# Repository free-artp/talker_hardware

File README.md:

Eagle project about ATMEGA168 for wood's sort device (p-dok.ru)

Print out:
	Bottom
	Pad
	Via
	Dimension
	Holes

Mirror + Pos.coord

Offcet:
X = 2.2 inch
Y = 7 inch

Hot iron - 40 sec, full power, by my hand not a body
11:38

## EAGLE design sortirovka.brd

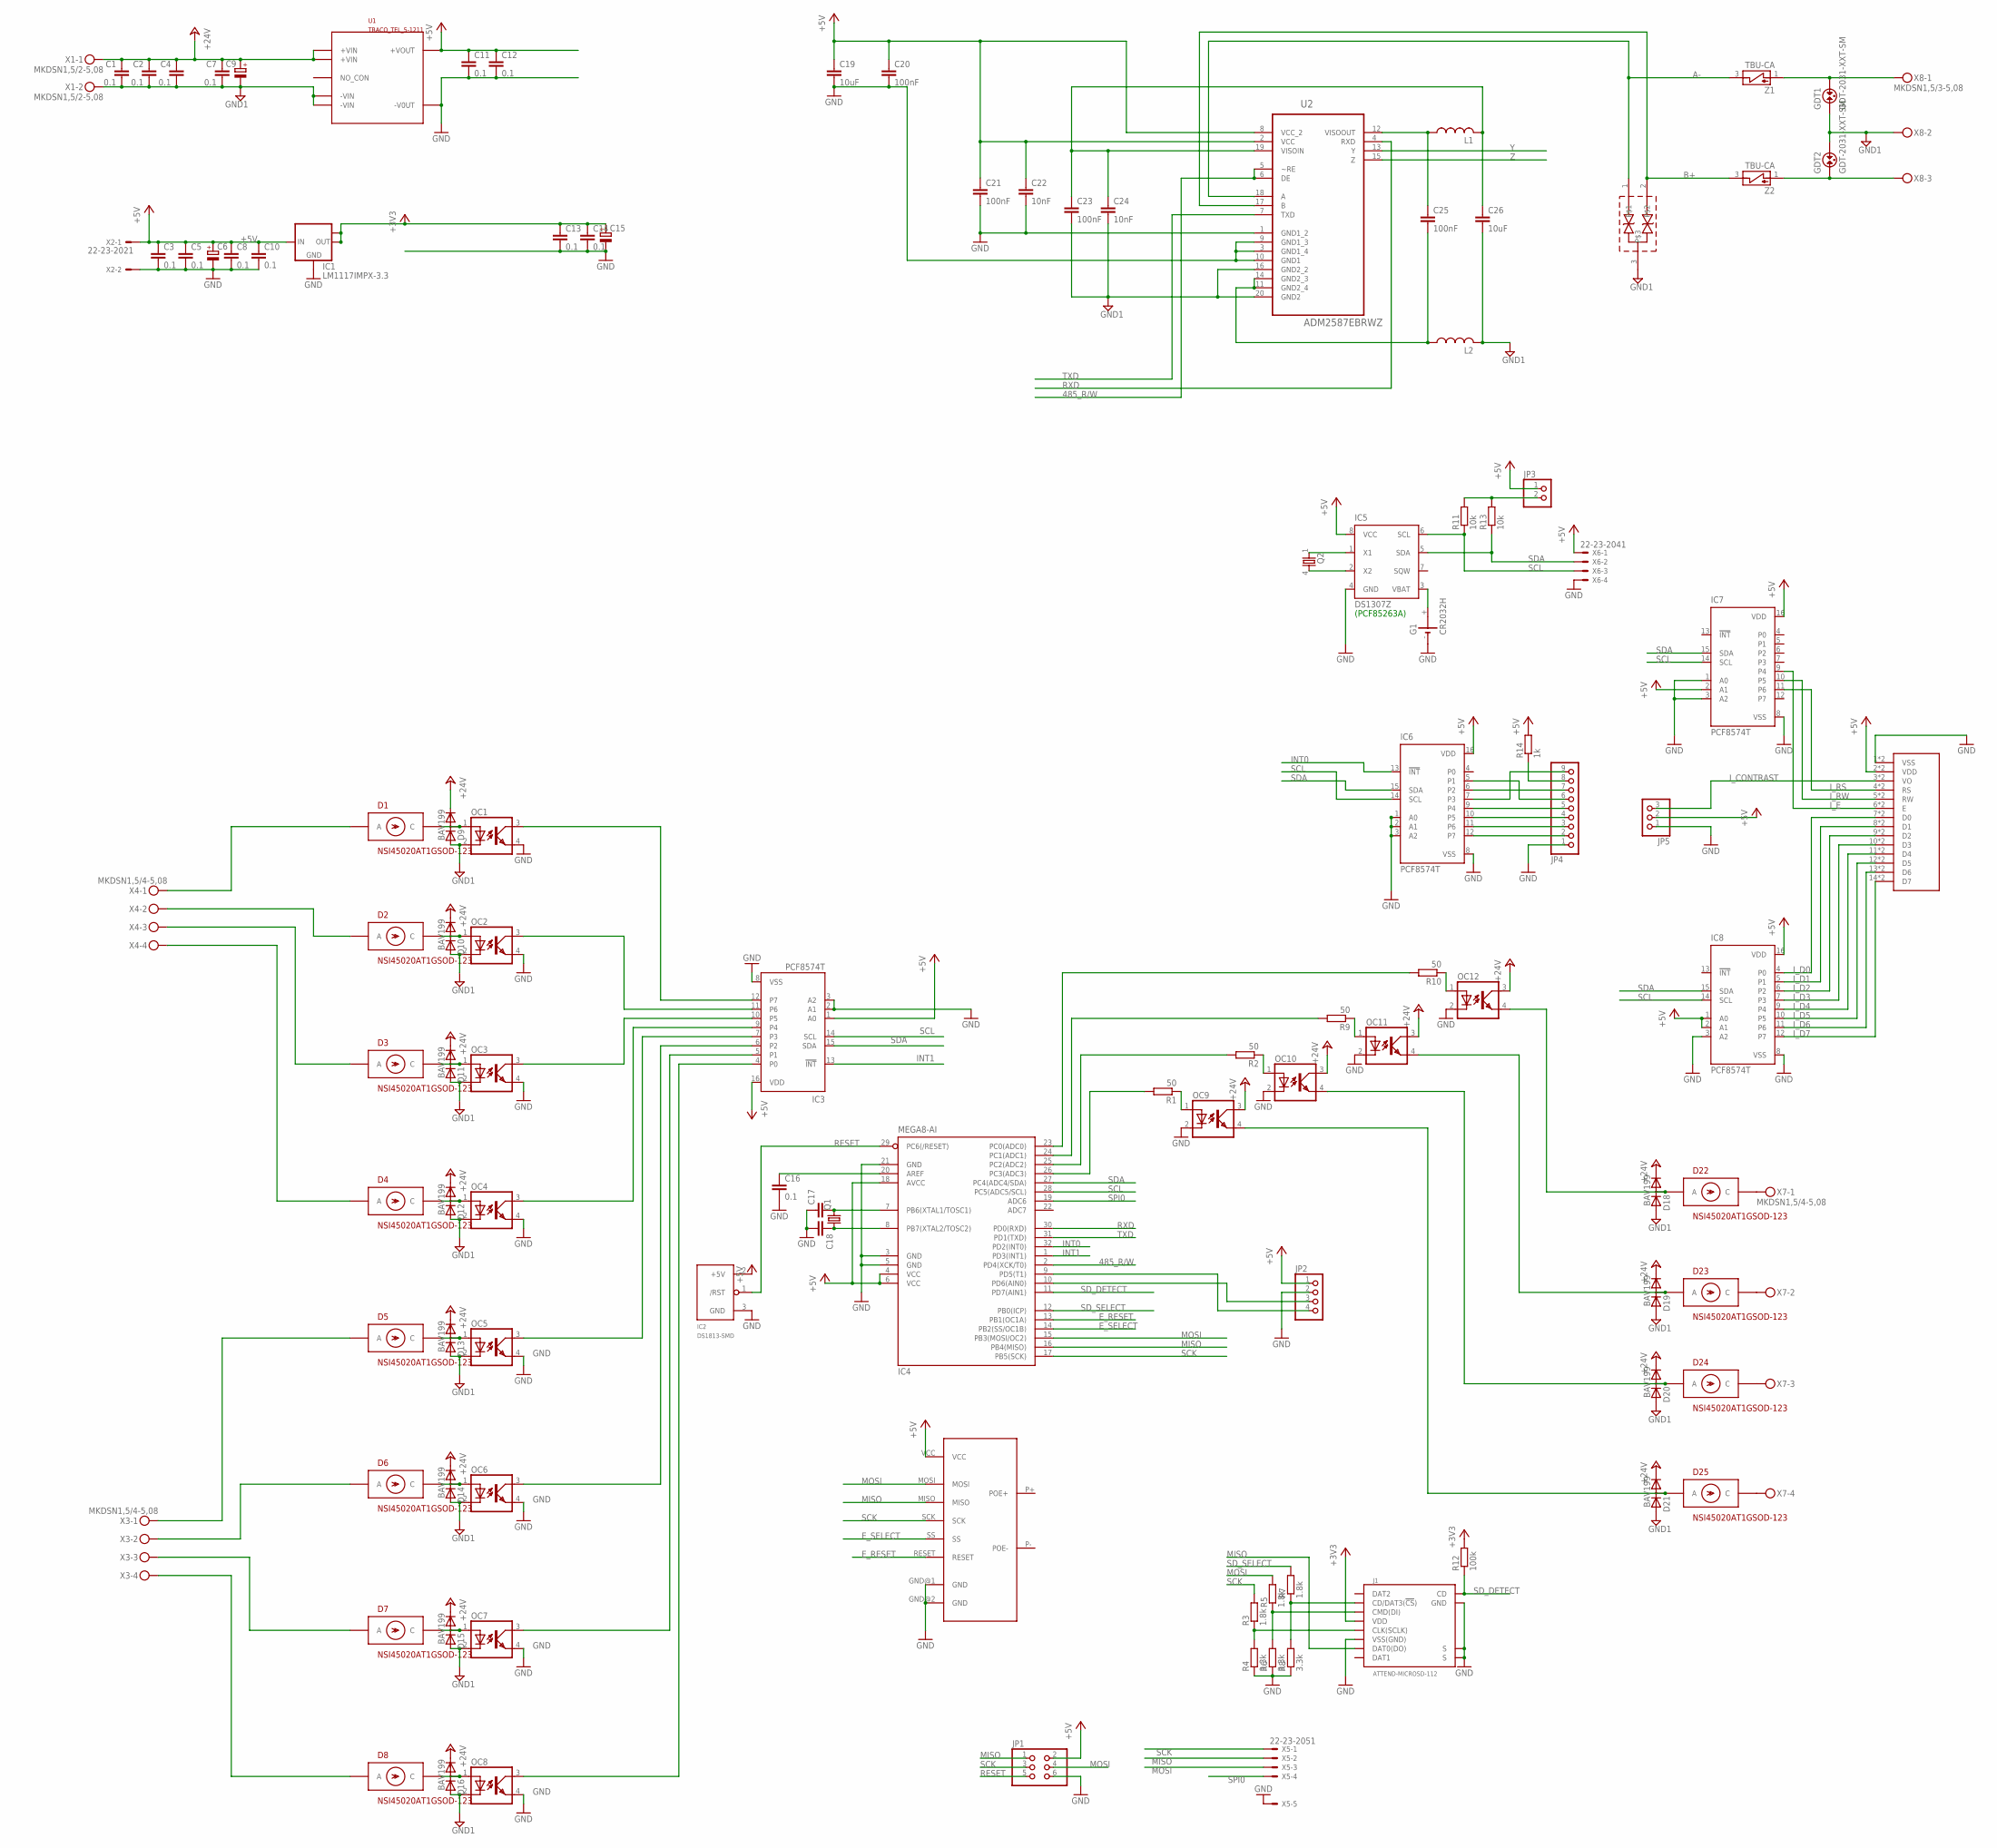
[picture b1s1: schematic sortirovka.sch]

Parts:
C1, C2, C3, C4, C5, C7, C8, C10, C11, C12, C13, C14, C16: 0.1; C0805
C6, C9, C15: CPOL-EU153CLV-0605; 153CLV-0605
C17, C18: C-EUC0805; C0805
C19, C26: 10uF; C0805
C20, C21, C23, C25: 100nF; C0805
C22, C24: 10nF; C0805
D1, D2, D3, D4, D5, D6, D7, D8, D22, D23, D24, D25: NSI45020AT1GSOD-123; SOD123
D9, D10, D11, D12, D13, D14, D15, D16, D18, D19, D20, D21: BAV199; SOT23
D17: CDSOT23-SM712SOT23-R; SOT23-R
G1: CR2032H
GDT1, GDT2: GDT-2031-XXT-SM; 2031-XXT-SM
IC1: LM1117IMPX-3.3; SOT223
IC2: DS1813-SMD; SOT-23
IC3, IC6, IC7, IC8: PCF8574T; SO16W
IC4: MEGA8-AI; TQFP32-08
IC5: DS1307Z; SOIC8
J1: ATTEND-MICROSD-112; ATTEND-112
JP1: PINHD-2X3; 2X03
JP2: PINHD-1X4; 1X04
JP3: PINHD-1X2; 1X02
JP4: PINHD-1X9; 1X09
JP5: PINHD-1X3; 1X03
L1, L2: L-US0402; L0402
LCD1: 2X16LCDBOTHM162SD07; 2X16LCDBOTH-1
MOD1: W5100_MODULESMALL; W5100_MODULE_1
OC1, OC2, OC3, OC4, OC5, OC6, OC7, OC8, OC9, OC10, OC11, OC12: SFH6106REAL; SFH6106
Q1: CRYSTALSM49; SM49
Q2: MA306
R1, R2, R9, R10: 50; R0805
R3, R5, R7: 1.8k; M0805
R4, R6, R8: 3.3k; M0805
R11, R13: 10k; R0805
R12: 100k; M0805
R14: 1k; R0805
U1: TRACO_TEL_5-1211; TRACO_POWER_TL5
U2: ADM2587EBRWZ; SOIC127P1032X265-20N
X1: MKDSN1,5/2-5,08
X2: 22-23-2021
X3, X4, X7: MKDSN1,5/4-5,08
X5: 22-23-2051
X6: 22-23-2041
X8: MKDSN1,5/3-5,08
Z1, Z2: TBU-CA

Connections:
485_R/W: IC4.2 (PD4(XCK/T0)), U2.5 (~RE), U2.6 (DE)
+3V3: C13.1, C14.1, C15.+, IC1.2 (OUT), IC1.TAB (OUT1), J1.VDD, R12.2
+5V: C3.1, C5.1, C6.+, C8.1, C10.1, C11.1, C12.1, C19.1, C20.1, C21.1, C22.1, IC1.3 (IN), IC2.2 (+5V), IC3.1 (A0), IC3.16 (VDD), IC4.4 (VCC), IC4.6 (VCC), IC4.18 (AVCC), IC5.8 (VCC), IC6.16 (VDD), IC7.2 (A1), IC7.16 (VDD), IC8.1 (A0), IC8.2 (A1), IC8.16 (VDD), JP1.2, JP2.1, JP3.1, JP5.2, LCD1.2 (VDD), LCD1.16 (VDD), MOD1.VCC, R14.2, U1.+VOUT, U2.2 (VCC), U2.8 (VCC_2), X2.1, X6.1
+24V: C1.1, C2.1, C4.1, C7.1, C9.+, D9.2 (C), D10.2 (C), D11.2 (C), D12.2 (C), D13.2 (C), D14.2 (C), D15.2 (C), D16.2 (C), D18.2 (C), D19.2 (C), D20.2 (C), D21.2 (C), OC9.3 (COL), OC10.3 (COL), OC11.3 (COL), OC12.3 (COL), U1.+VIN@1 (+VIN), U1.+VIN@2 (+VIN), X1.1
A-: D17.1, U2.18 (A), Z1.3 (2)
B+: D17.2, U2.17 (B), Z2.3 (2)
E_RESET: IC4.13 (PB1(OC1A)), MOD1.RESET
E_SELECT: IC4.14 (PB2(SS/OC1B)), MOD1.SS
GND: C3.2, C5.2, C6.-, C8.2, C10.2, C11.2, C12.2, C13.2, C14.2, C15.-, C16.2, C17.1, C18.2, C19.2, C20.2, C21.2, C22.2, G1.-, IC1.1 (GND), IC2.3 (GND), IC3.2 (A1), IC3.3 (A2), IC3.8 (VSS), IC4.3 (GND), IC4.5 (GND), IC4.21 (GND), IC5.4 (GND), IC6.1 (A0), IC6.2 (A1), IC6.3 (A2), IC6.8 (VSS), IC7.1 (A0), IC7.3 (A2), IC7.8 (VSS), IC8.3 (A2), IC8.8 (VSS), J1.GND, J1.S1 (S), J1.S2 (S), J1.VSS (VSS(GND)), JP1.6, JP2.2, JP4.1, JP5.1, LCD1.1 (VSS), LCD1.15 (VSS), MOD1.GND@1 (GND), MOD1.GND@2 (GND), OC1.4 (EMIT), OC2.4 (EMIT), OC3.4 (EMIT), OC4.4 (EMIT), OC5.4 (EMIT), OC6.4 (EMIT), OC7.4 (EMIT), OC8.4 (EMIT), OC9.2 (C), OC10.2 (C), OC11.2 (C), OC12.2 (C), R4.1, R6.1, R8.1, U1.-VOUT (-V0UT), U2.1 (GND1_2), U2.3 (GND1_4), U2.9 (GND1_3), U2.10 (GND1), X2.2, X5.5, X6.4
GND1: C1.2, C2.2, C4.2, C7.2, C9.-, C23.2, C24.2, C26.2, D9.1 (A), D10.1 (A), D11.1 (A), D12.1 (A), D13.1 (A), D14.1 (A), D15.1 (A), D16.1 (A), D17.3, D18.1 (A), D19.1 (A), D20.1 (A), D21.1 (A), GDT1.1, GDT2.2, L2.2, OC1.2 (C), OC2.2 (C), OC3.2 (C), OC4.2 (C), OC5.2 (C), OC6.2 (C), OC7.2 (C), OC8.2 (C), U1.-VIN@1 (-VIN), U1.-VIN@2 (-VIN), U2.16 (GND2_2), U2.20 (GND2), X1.2, X8.2
INT0: IC4.32 (PD2(INT0)), IC6.13 (!INT)
INT1: IC3.13 (!INT), IC4.1 (PD3(INT1))
I_CONTRAST: JP5.3, LCD1.3 (VO), LCD1.17 (VO)
I_D0: IC8.4 (P0), LCD1.7 (D0), LCD1.21 (D0)
I_D1: IC8.5 (P1), LCD1.8 (D1), LCD1.22 (D1)
I_D2: IC8.6 (P2), LCD1.9 (D2), LCD1.23 (D2)
I_D3: IC8.7 (P3), LCD1.10 (D3), LCD1.24 (D3)
I_D4: IC8.9 (P4), LCD1.11 (D4), LCD1.25 (D4)
I_D5: IC8.10 (P5), LCD1.12 (D5), LCD1.26 (D5)
I_D6: IC8.11 (P6), LCD1.13 (D6), LCD1.27 (D6)
I_D7: IC8.12 (P7), LCD1.14 (D7), LCD1.28 (D7)
I_E: IC7.9 (P4), LCD1.6 (E), LCD1.20 (E)
I_RS: IC7.11 (P6), LCD1.4 (RS), LCD1.18 (RS)
I_RW: IC7.10 (P5), LCD1.5 (RW), LCD1.19 (RW)
MISO: IC4.16 (PB4(MISO)), J1.DAT0 (DAT0(DO)), JP1.1, MOD1.MISO, X5.2
MOSI: IC4.15 (PB3(MOSI/OC2)), JP1.4, MOD1.MOSI, R5.2, X5.3
unnamed: GDT1.2, X8.1, Z1.1
unnamed: GDT2.1, X8.3, Z2.1
unnamed: C23.1, C24.1, C26.1, L1.2, U2.19 (VISOIN)
unnamed: C25.2, L2.1, U2.11 (GND2_4), U2.14 (GND2_3)
unnamed: C25.1, L1.1, U2.12 (VISOOUT)
unnamed: IC4.23 (PC0(ADC0)), R10.2
unnamed: IC4.24 (PC1(ADC1)), R9.2
unnamed: IC4.25 (PC2(ADC2)), R2.2
unnamed: IC4.26 (PC3(ADC3)), R1.2
unnamed: D18.3 (AC), D22.A, OC12.4 (EMIT)
unnamed: D19.3 (AC), D23.A, OC11.4 (EMIT)
unnamed: D20.3 (AC), D24.A, OC10.4 (EMIT)
unnamed: D21.3 (AC), D25.A, OC9.4 (EMIT)
unnamed: C18.1, IC4.8 (PB7(XTAL2/TOSC2)), Q1.1
unnamed: OC9.1 (A), R1.1
unnamed: D1.C, D9.3 (AC), OC1.1 (A)
unnamed: D2.C, D10.3 (AC), OC2.1 (A)
unnamed: OC10.1 (A), R2.1
unnamed: OC11.1 (A), R9.1
unnamed: G1.+, IC5.3 (VBAT)
unnamed: D1.A, X4.1
unnamed: D2.A, X4.2
unnamed: IC5.1 (X1), Q2.1
unnamed: D3.C, D11.3 (AC), OC3.1 (A)
unnamed: IC5.2 (X2), Q2.4 (2)
unnamed: C17.2, IC4.7 (PB6(XTAL1/TOSC1)), Q1.2
unnamed: D4.C, D12.3 (AC), OC4.1 (A)
unnamed: D7.A, X3.3
unnamed: OC12.1 (A), R10.1
unnamed: D5.C, D13.3 (AC), OC5.1 (A)
unnamed: D6.C, D14.3 (AC), OC6.1 (A)
unnamed: D4.A, X4.4
unnamed: D7.C, D15.3 (AC), OC7.1 (A)
unnamed: D3.A, X4.3
unnamed: D8.C, D16.3 (AC), OC8.1 (A)
unnamed: D5.A, X3.1
unnamed: D6.A, X3.2
unnamed: D8.A, X3.4
unnamed: IC3.6 (P2), OC6.3 (COL)
unnamed: IC3.5 (P1), OC7.3 (COL)
unnamed: IC3.4 (P0), OC8.3 (COL)
unnamed: J1.DAT3 (CD/DAT3(!CS!)), R7.1, R8.2
unnamed: IC6.12 (P7), JP4.2
unnamed: IC6.11 (P6), JP4.3
unnamed: IC6.10 (P5), JP4.4
unnamed: IC6.5 (P1), JP4.6
unnamed: IC6.9 (P4), JP4.5
unnamed: IC6.7 (P3), JP4.9
unnamed: IC6.6 (P2), JP4.7
unnamed: JP4.8, R14.1
unnamed: IC3.12 (P7), OC1.3 (COL)
unnamed: IC3.11 (P6), OC2.3 (COL)
unnamed: IC3.10 (P5), OC3.3 (COL)
unnamed: IC3.9 (P4), OC4.3 (COL)
unnamed: IC3.7 (P3), OC5.3 (COL)
unnamed: J1.CMD (CMD(DI)), R5.1, R6.2
unnamed: J1.CLK (CLK(SCLK)), R3.1, R4.2
unnamed: C16.1, IC4.20 (AREF)
unnamed: D22.C, X7.1
unnamed: D23.C, X7.2
unnamed: IC4.10 (PD6(AIN0)), JP2.3
unnamed: D24.C, X7.3
unnamed: IC4.9 (PD5(T1)), JP2.4
unnamed: D25.C, X7.4
unnamed: JP3.2, R11.2, R13.2
RESET: IC2.1 (/RST), IC4.29 (PC6(/RESET)), JP1.5
RXD: IC4.30 (PD0(RXD)), U2.4 (RXD)
SCK: IC4.17 (PB5(SCK)), JP1.3, MOD1.SCK, R3.2, X5.1
SCL: IC3.14 (SCL), IC4.28 (PC5(ADC5/SCL)), IC5.6 (SCL), IC6.14 (SCL), IC7.14 (SCL), IC8.14 (SCL), R11.1, X6.3
SDA: IC3.15 (SDA), IC4.27 (PC4(ADC4/SDA)), IC5.5 (SDA), IC6.15 (SDA), IC7.15 (SDA), IC8.15 (SDA), R13.1, X6.2
SD_DETECT: IC4.11 (PD7(AIN1)), J1.CD, R12.1
SD_SELECT: IC4.12 (PB0(ICP)), R7.2
SPI0: IC4.19 (ADC6), X5.4
TXD: IC4.31 (PD1(TXD)), U2.7 (TXD)
Y: U2.13 (Y)
Z: U2.15 (Z)

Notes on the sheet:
(PCF85263A)

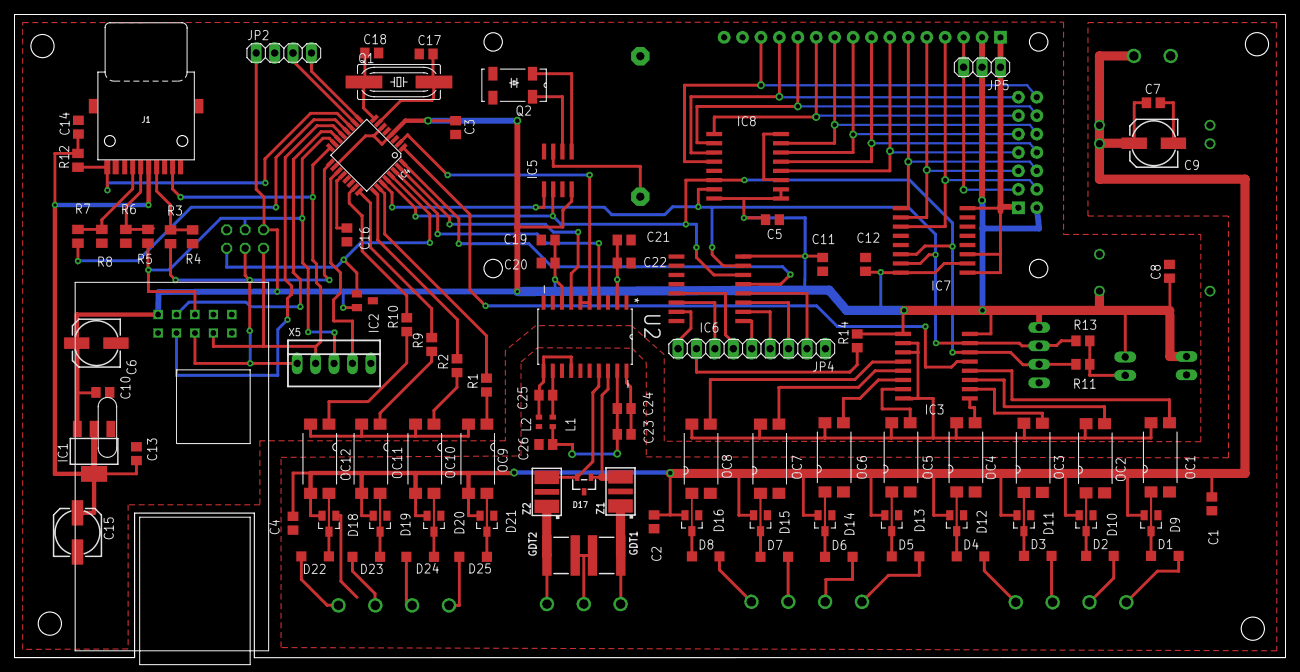
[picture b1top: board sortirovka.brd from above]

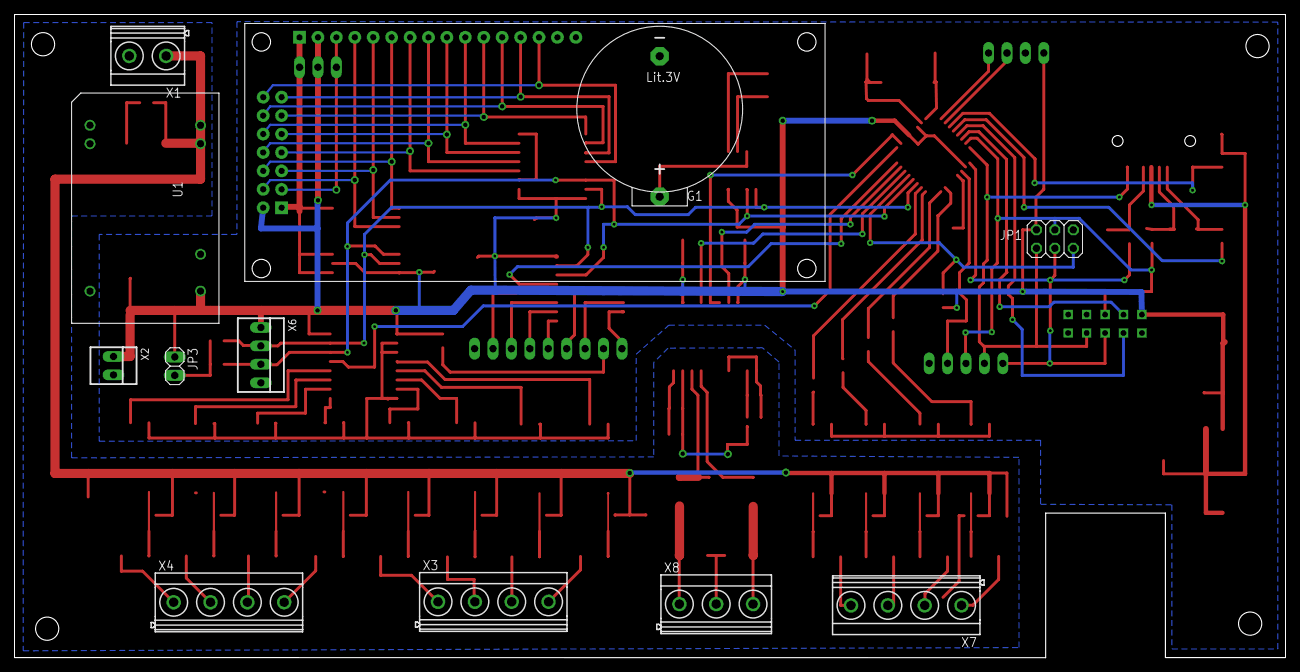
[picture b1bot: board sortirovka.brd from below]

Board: 2 copper layers, 175.2 x 88.7 mm, 112 parts (12 on the bottom side), 100 nets.

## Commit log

2017-06-19 rev1
2017-06-19 rev2 5-input 4-output
2017-06-22 rev1.0 to produce
2017-06-24 some changes in packages
2017-07-05 rev 1.1 to produce
2017-07-06 manufacture-1
2017-09-15 initial
2017-09-15 Add I2C RTC
2017-09-15 traced I2C
2017-09-21 could be produced
2017-09-21 not diode - supreesor
2017-09-22 current source for optocoupler, old design
2017-09-27 main pars on the board
2017-10-10 All routed.
2017-10-10 image
2017-10-11 Ready to gerber
2017-10-18 Prepared to rezonver

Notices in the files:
parts and their libraries:
supressor: Copyright (C) 2009, Bob Starr
